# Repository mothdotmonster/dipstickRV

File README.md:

# dipstickRV
adorably small CH32V003 devboard

[buy it here](https://mothdotmonster-shop.square.site/product/dipstickrv/7)

includes user-LED on PD6 and [rv003usb](https://github.com/cnlohr/rv003usb)-compatible USB-C port

uses [Paw-Connect](https://github.com/LeoDJ/Paw-Connect)

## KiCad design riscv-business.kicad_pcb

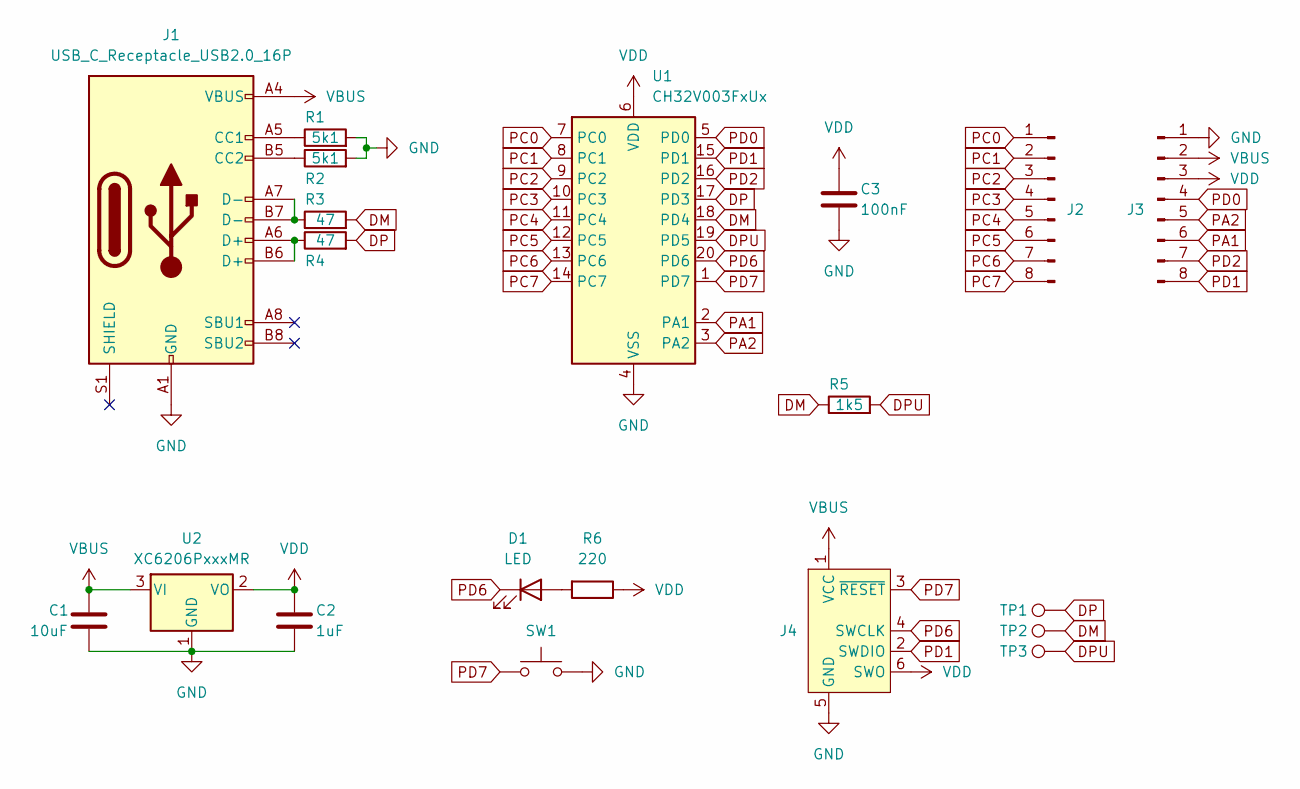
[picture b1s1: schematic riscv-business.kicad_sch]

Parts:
C1: 10uF; C_0402_1005Metric; JLC C15525
C2: 1uF; C_0402_1005Metric; JLC C52923
C3: 100nF; C_0402_1005Metric; JLC C1525
D1: LED; LED_0603_1608Metric; JLC C2286
J1: USB_C_Receptacle_USB2.0_16P; USB_C_Receptacle_HCTL_HC-TYPE-C-16P-01A; JLC C2765186
J2, J3: Conn_01x08_Pin; PinHeader_1x08_P2.54mm_Vertical
J4: Conn_ARM_SWD_TagConnect_TC2030-NL; Paw-Connect_RevA_TC2030-IDC-NL_2x03_P1.27mm_Vertical
R1, R2: 5k1; R_0402_1005Metric; JLC C25905
R3, R4: 47; R_0402_1005Metric; JLC C25105
R5: 1k5; R_0402_1005Metric; JLC C25867
R6: 220; R_0402_1005Metric; JLC C25091
SW1: SW_Push; Panasonic-EVPAW-2x3mm; JLC C2858607
TP1, TP2, TP3: TestPoint; TestPoint_Pad_D1.0mm
U1: CH32V003FxUx; QFN-20-1EP_3x3mm_P0.4mm_EP1.65x1.65mm; JLC C5299908
U2: XC6206PxxxMR; SOT-23-3; JLC C5446

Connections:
DM: R3.2, R5.1, TP2.1, U1.18 (PD4)
DP: R4.2, TP1.1, U1.17 (PD3)
DPU: R5.2, TP3.1, U1.19 (PD5)
GND: C1.2, C2.2, C3.2, J1.A1 (GND), J1.A12 (GND), J1.B1 (GND), J1.B12 (GND), J3.1, J4.5 (GND), R1.2, R2.2, SW1.2, U1.4 (VSS), U1.21 (VSS), U2.1 (GND)
unnamed: D1.2 (A), R6.2
unnamed: J1.A5 (CC1), R1.1
unnamed: J1.B5 (CC2), R2.1
unnamed: J1.A6 (D+), J1.B6 (D+), R4.1
unnamed: J1.A7 (D-), J1.B7 (D-), R3.1
PA1: J3.6, U1.2 (PA1)
PA2: J3.5, U1.3 (PA2)
PC0: J2.1, U1.7 (PC0)
PC1: J2.2, U1.8 (PC1)
PC2: J2.3, U1.9 (PC2)
PC3: J2.4, U1.10 (PC3)
PC4: J2.5, U1.11 (PC4)
PC5: J2.6, U1.12 (PC5)
PC6: J2.7, U1.13 (PC6)
PC7: J2.8, U1.14 (PC7)
PD0: J3.4, U1.5 (PD0)
PD1: J3.8, J4.2 (SWDIO), U1.15 (PD1)
PD2: J3.7, U1.16 (PD2)
PD6: D1.1 (K), J4.4 (SWCLK), U1.20 (PD6)
PD7: J4.3 (~RESET), SW1.1, U1.1 (PD7)
VBUS: C1.1, J1.A4 (VBUS), J1.A9 (VBUS), J1.B4 (VBUS), J1.B9 (VBUS), J3.2, J4.1 (VCC), U2.3 (VI)
VDD: C2.1, C3.1, J3.3, J4.6 (SWO), R6.1, U1.6 (VDD), U2.2 (VO)

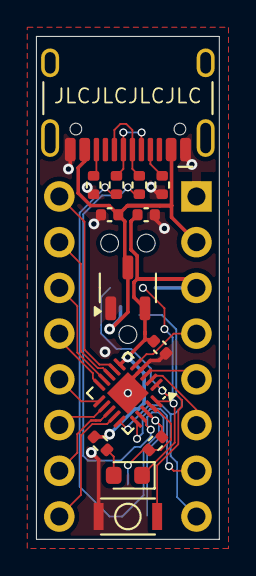
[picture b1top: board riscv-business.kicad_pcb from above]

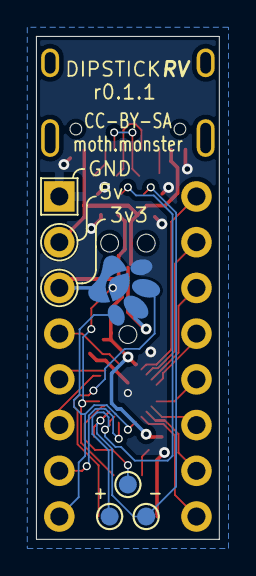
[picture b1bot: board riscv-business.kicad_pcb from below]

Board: 2 copper layers, 10.2 x 27.9 mm, 20 parts (6 on the bottom side), 26 nets.

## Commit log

2024-10-22 add license
2024-10-25 add nice pinout diagram

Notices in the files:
riscv-business.kicad_pcb:
CC-BY-SA
